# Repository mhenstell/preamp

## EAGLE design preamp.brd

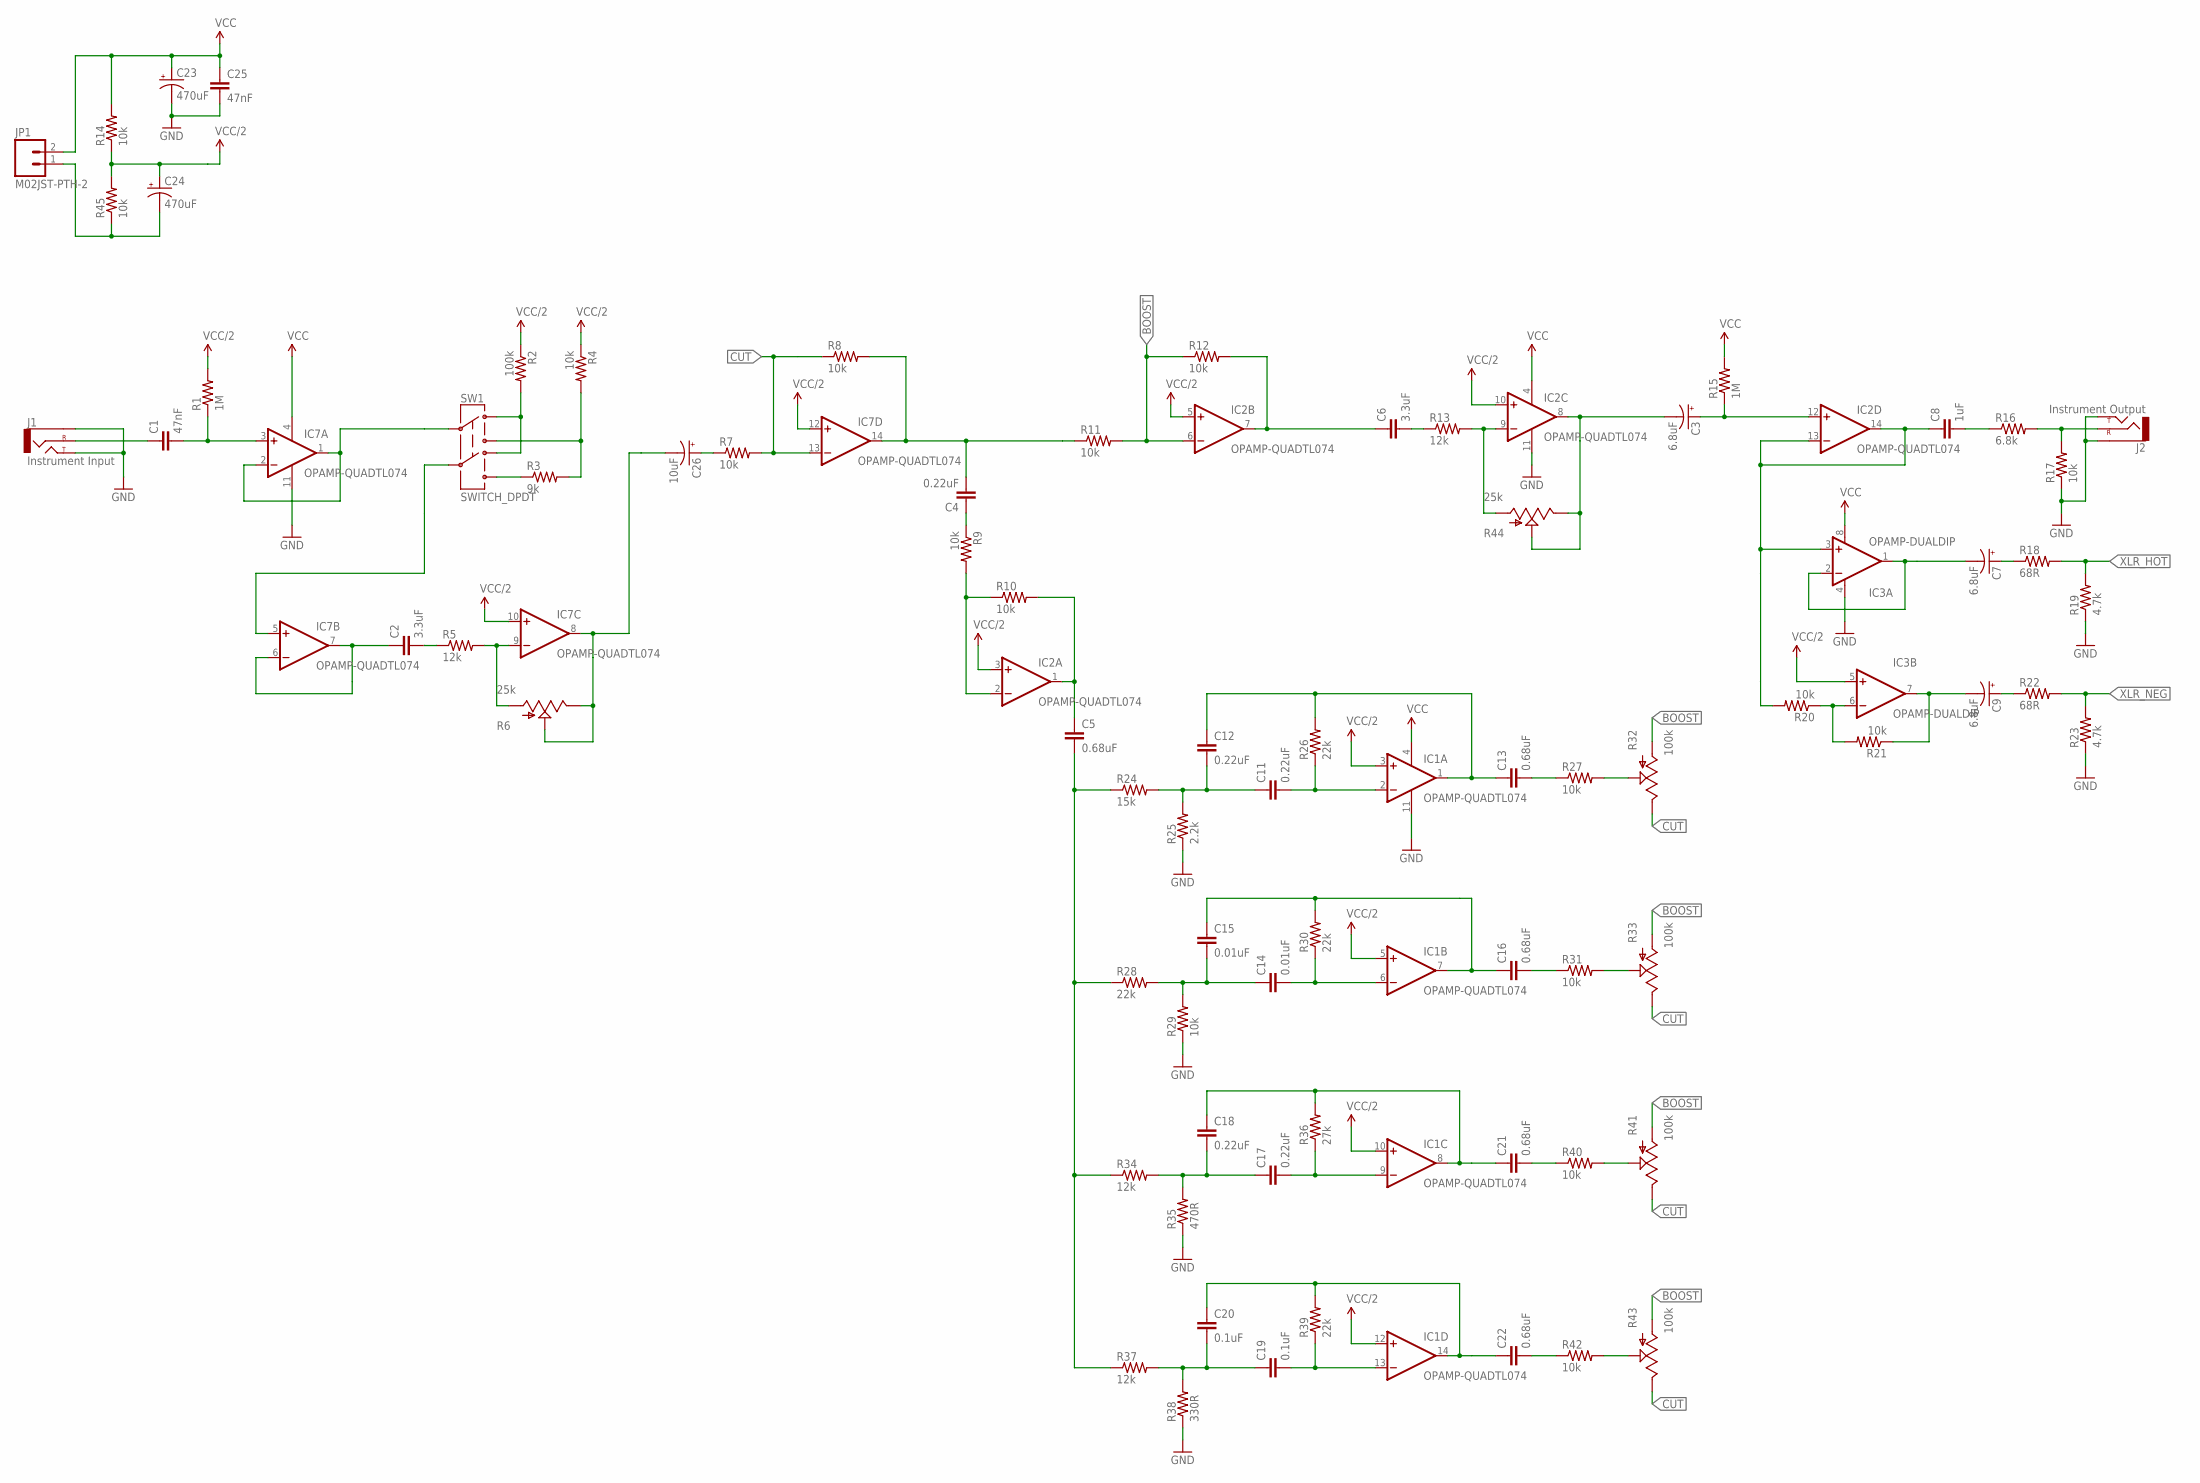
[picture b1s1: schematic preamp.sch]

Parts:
C1, C25: 47nF; CAP-5MM; PARTNO FK28X7R1H473K
C2, C6: 3.3uF; CAP-5MM; PARTNO FK28X5R1A335K
C3, C7, C9: 6.8uF; CPOL-RADIAL-10UF-25V; PARTNO ESH685M063AC3AA
C4, C11, C12, C17, C18: 0.22uF; CAP-5MM; PARTNO FK28X7R1C224K
C5, C13, C16, C21, C22: 0.68uF; CAP-5MM; PARTNO FK28X5R1A684K
C8: 1uF; CAP-5MM
C14, C15: 0.01uF; CAP-5MM
C19, C20: 0.1uF; CAP-5MM
C23, C24: 470uF; CPOL-RADIAL-100UF-25V
C26: 10uF; CPOL-RADIAL-10UF-25V
IC1, IC2, IC7: OPAMP-QUADTL074; DIP14; PARTNO TL074CN
IC3: OPAMP-DUALDIP; DIP08; PARTNO TL072IP
J1: Instrument Input; AUDIO-JACK-RA49B12B
J2: Instrument Output; AUDIO-JACK-RA49B12B
JP1: M02JST-PTH-2; JST-2-PTH
R1, R15: 1M; AXIAL-0.4; PARTNO CF14JT1M00
R2: 100k; AXIAL-0.4; PARTNO CF14JT100K
R3: 9k; AXIAL-0.4; PARTNO CF14JT9K10
R4, R7, R8, R9, R10, R11, R12, R14, R17, R20, R21, R27, R29, R31, R40, R42, R45: 10k; AXIAL-0.4; PARTNO CF14JT10K0
R5, R13, R34, R37: 12k; AXIAL-0.4; PARTNO CF14JT12K0
R6, R44: 25k; POTENTIOMETER-EVUE2A; PARTNO EVU-E2AF25D24
R16: 6.8k; AXIAL-0.4; PARTNO CF14JT6K80
R18, R22: 68R; AXIAL-0.4; PARTNO CF14JT68R0
R19, R23: 4.7k; AXIAL-0.4; PARTNO CF14JT4K70
R24: 15k; AXIAL-0.4; PARTNO CF14JT15K0
R25: 2.2k; AXIAL-0.4; PARTNO CF14JT2K20
R26, R28, R30, R39: 22k; AXIAL-0.4; PARTNO CF14JT22K0
R32, R33, R41, R43: 100k; POTENTIOMETER-PTV09A-2020F-B104; PARTNO PTV09A-2020F-B104
R35: 470R; AXIAL-0.4
R36: 27k; AXIAL-0.4
R38: 330R; AXIAL-0.4
SW1: SWITCH_DPDT; SWITCH-EG2211

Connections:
BOOST: IC2.6 (IN-), R11.P$2 (2), R12.P$1 (1), R32.3 (A), R33.3 (A), R41.3 (A), R43.3 (A)
CUT: IC7.13 (IN-), R7.P$2 (2), R8.P$1 (1), R32.1 (E), R33.1 (E), R41.1 (E), R43.1 (E)
GND: C23.2 (-), C25.2, IC1.11 (VEE), IC2.11 (VEE), IC3.4 (V-), IC7.11 (VEE), J1.S (SLEEVE), J1.T (TIP), J2.S (SLEEVE), J2.T (TIP), R17.P$1 (1), R19.P$1 (1), R23.P$1 (1), R25.P$1 (1), R29.P$1 (1), R35.P$1 (1), R38.P$1 (1)
unnamed: C1.1, J1.R (RING)
unnamed: C1.2, IC7.3 (IN+), R1.P$1 (1)
unnamed: IC7.9 (IN-), R5.P$2 (2), R6.1 (A)
unnamed: R2.P$2 (2), SW1.L1, SW1.L2
unnamed: IC7.5 (IN+), SW1.C2
unnamed: R3.P$2 (2), R4.P$2 (2), SW1.R1
unnamed: R3.P$1 (1), SW1.R2
unnamed: C2.1, IC7.6 (IN-), IC7.7 (OUT)
unnamed: C2.2, R5.P$1 (1)
unnamed: C26.2 (-), IC7.8 (OUT), R6.2 (S), R6.3 (E)
unnamed: IC2.9 (IN-), R13.P$2 (2), R44.1 (A)
unnamed: C26.1 (+), R7.P$1 (1)
unnamed: C4.2, IC7.14 (OUT), R8.P$2 (2), R11.P$1 (1)
unnamed: C4.1, R9.P$1 (1)
unnamed: IC2.2 (IN-), R9.P$2 (2), R10.P$1 (1)
unnamed: C5.1, IC2.1 (OUT), R10.P$2 (2)
unnamed: C6.1, IC2.7 (OUT), R12.P$2 (2)
unnamed: C6.2, R13.P$1 (1)
unnamed: C5.2, R24.P$1 (1), R28.P$1 (1), R34.P$1 (1), R37.P$1 (1)
unnamed: C3.2 (-), IC2.8 (OUT), R44.2 (S), R44.3 (E)
unnamed: C3.1 (+), IC2.12 (IN+), R15.P$1 (1)
unnamed: C8.1, IC2.13 (IN-), IC2.14 (OUT), IC3.3 (+IN), R20.P$2 (2)
unnamed: C8.2, R16.P$1 (1)
unnamed: J2.R (RING), R16.P$2 (2), R17.P$2 (2)
unnamed: C7.2 (-), IC3.1 (OUT), IC3.2 (-IN)
unnamed: C7.1 (+), R18.P$1 (1)
unnamed: IC3.6 (-IN), R20.P$1 (1), R21.P$2 (2)
unnamed: C9.2 (-), IC3.7 (OUT), R21.P$1 (1)
unnamed: C9.1 (+), R22.P$1 (1)
unnamed: C11.2, IC1.2 (IN-), R26.P$1 (1)
unnamed: C12.1, C13.1, IC1.1 (OUT), R26.P$2 (2)
unnamed: C11.1, C12.2, R24.P$2 (2), R25.P$2 (2)
unnamed: C13.2, R27.P$1 (1)
unnamed: C14.2, IC1.6 (IN-), R30.P$1 (1)
unnamed: C15.1, C16.1, IC1.7 (OUT), R30.P$2 (2)
unnamed: C14.1, C15.2, R28.P$2 (2), R29.P$2 (2)
unnamed: R27.P$2 (2), R32.2 (S)
unnamed: C16.2, R31.P$1 (1)
unnamed: R31.P$2 (2), R33.2 (S)
unnamed: C17.2, IC1.9 (IN-), R36.P$1 (1)
unnamed: C18.1, C21.1, IC1.8 (OUT), R36.P$2 (2)
unnamed: C17.1, C18.2, R34.P$2 (2), R35.P$2 (2)
unnamed: C19.2, IC1.13 (IN-), R39.P$1 (1)
unnamed: IC7.1 (OUT), IC7.2 (IN-), SW1.C1
unnamed: C19.1, C20.2, R37.P$2 (2), R38.P$2 (2)
unnamed: C24.2 (-), JP1.1, R45.P$1 (1)
unnamed: C21.2, R40.P$1 (1)
unnamed: R40.P$2 (2), R41.2 (S)
unnamed: C20.1, C22.1, IC1.14 (OUT), R39.P$2 (2)
unnamed: C22.2, R42.P$1 (1)
unnamed: R42.P$2 (2), R43.2 (S)
VCC: C23.1 (+), C25.1, IC1.4 (VCC), IC2.4 (VCC), IC3.8 (V+), IC7.4 (VCC), JP1.2, R14.P$2 (2), R15.P$2 (2)
VCC/2: C24.1 (+), IC1.3 (IN+), IC1.5 (IN+), IC1.10 (IN+), IC1.12 (IN+), IC2.3 (IN+), IC2.5 (IN+), IC2.10 (IN+), IC3.5 (+IN), IC7.10 (IN+), IC7.12 (IN+), R1.P$2 (2), R2.P$1 (1), R4.P$1 (1), R14.P$1 (1), R45.P$2 (2)
XLR_HOT: R18.P$2 (2), R19.P$2 (2)
XLR_NEG: R22.P$2 (2), R23.P$2 (2)

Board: 2 copper layers, 78 parts (0 on the bottom side), 58 nets, no tracks yet.

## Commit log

2014-05-30 preamp init
2014-06-05 fixed schematic, started layout
2014-06-05 updated board size

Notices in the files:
parts and their libraries:
SparkFun-Capacitors: Licensing: CC v3.0 Share-Alike You are welcome to use this library for commercial purposes.
